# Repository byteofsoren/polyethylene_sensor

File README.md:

# polyethylene_sensor
Using High Density Conductive Polyethylene Black Foam as a restive sensor to build spatial object awareness in robotic grippers

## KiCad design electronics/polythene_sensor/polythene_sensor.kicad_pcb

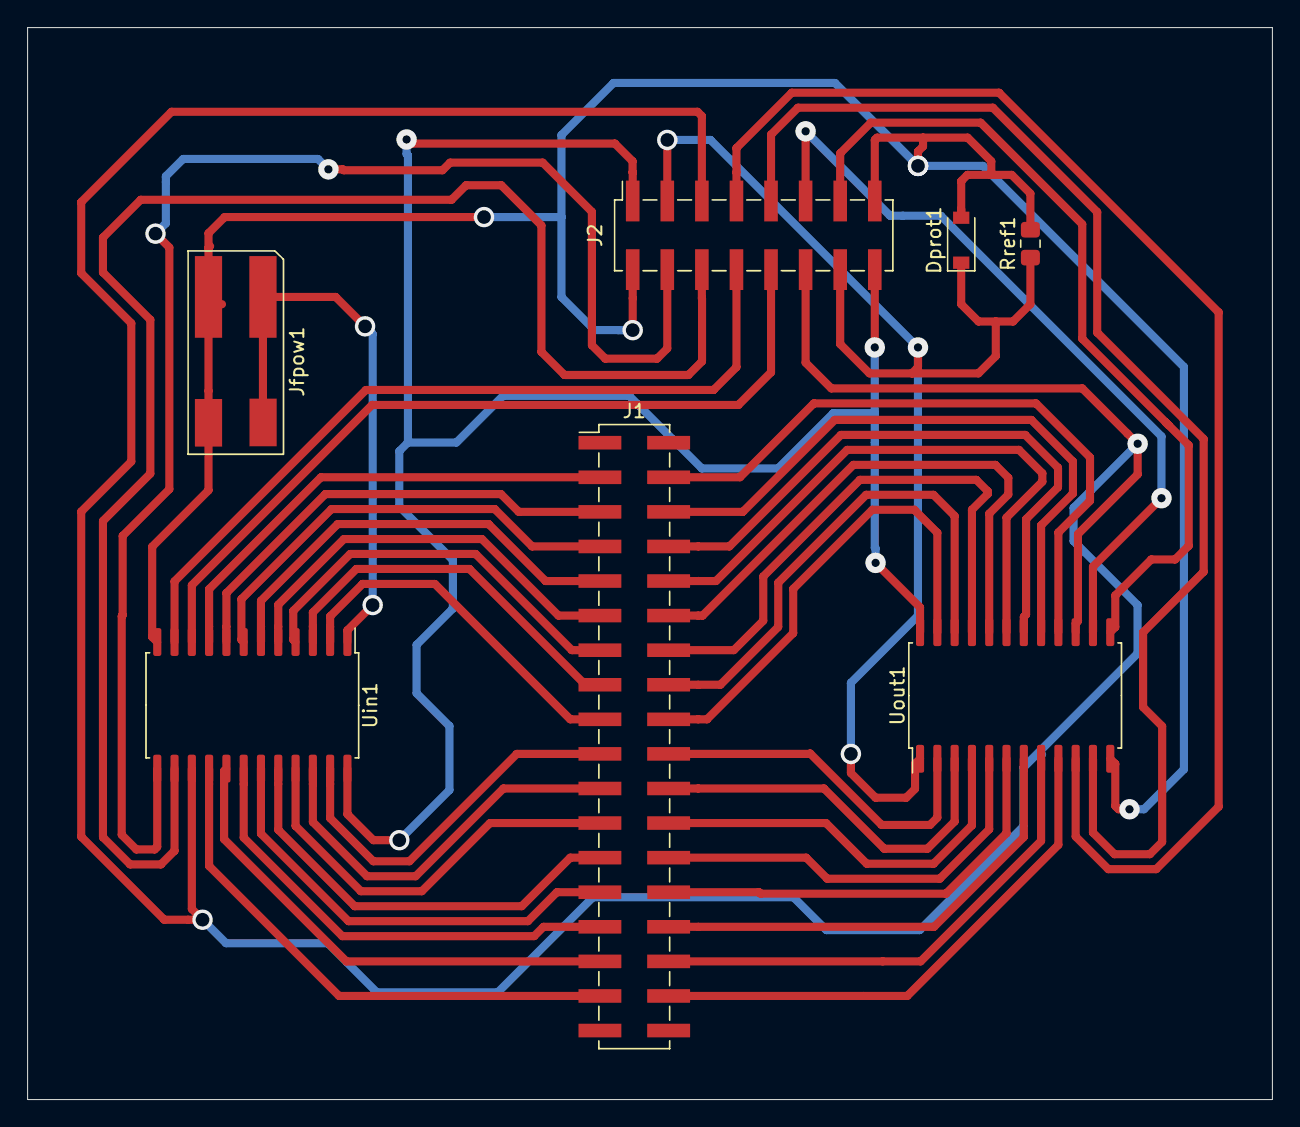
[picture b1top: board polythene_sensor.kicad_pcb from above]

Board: 2 copper layers, 91.4 x 78.7 mm, 7 parts (0 on the bottom side), 45 nets.

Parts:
Dprot1: BZT52Bxx; D_SOD-123
J1: Conn_02x18_Odd_Even; PinHeader_2x18_P2.54mm_Vertical_SMD
J2: Conn_02x08_Odd_Even; PinSocket_2x08_P2.54mm_Vertical_SMD
Jfpow1: Conn_01x02; MOLEX_104188
Rref1: R; R_0805_2012Metric_Pad1.15x1.40mm_HandSolder
Uin1: CD74HC4067M; SOIC-24W_7.5x15.4mm_P1.27mm
Uout1: CD74HC4067M; SOIC-24W_7.5x15.4mm_P1.27mm

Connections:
+5V: J2.1, J2.16, Uin1.24, Uout1.24
/EN: J2.5, J2.12, Uin1.15, Uout1.15
/S0: J2.13, Uout1.13
/S1: J2.11, Uout1.14
/S2: J2.9, Uout1.11
/S3: J2.7, Uout1.10
/S4: J2.10, Uin1.10
/S5: J2.8, Uin1.11
/S6: J2.6, Uin1.14
/S7: J2.4, Uin1.13
GND: Dprot1.2, J2.2, J2.15, Jfpow1.2, Rref1.2, Uin1.12, Uout1.12
unnamed: Dprot1.1, J2.3, J2.14, Rref1.1, Uout1.1
unnamed: J1.3, Uin1.9
unnamed: J1.4, Uout1.16
unnamed: J1.5, Uin1.8
unnamed: J1.6, Uout1.17
unnamed: J1.7, Uin1.7
unnamed: J1.8, Uout1.18
unnamed: J1.9, Uin1.6
unnamed: J1.10, Uout1.19
unnamed: J1.11, Uin1.5
unnamed: J1.12, Uout1.20
unnamed: J1.13, Uin1.4
unnamed: J1.14, Uout1.21
unnamed: J1.15, Uin1.3
unnamed: J1.16, Uout1.22
unnamed: J1.17, Uin1.2
unnamed: J1.18, Uout1.23
unnamed: J1.19, Uin1.23
unnamed: J1.20, Uout1.2
unnamed: J1.21, Uin1.22
unnamed: J1.22, Uout1.3
unnamed: J1.23, Uin1.21
unnamed: J1.24, Uout1.4
unnamed: J1.25, Uin1.20
unnamed: J1.26, Uout1.5
unnamed: J1.27, Uin1.19
unnamed: J1.28, Uout1.6
unnamed: J1.29, Uin1.18
unnamed: J1.30, Uout1.7
unnamed: J1.31, Uin1.17
unnamed: J1.32, Uout1.8
unnamed: J1.33, Uin1.16
unnamed: J1.34, Uout1.9
unnamed: Jfpow1.1, Uin1.1

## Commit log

2019-05-01 start project
2019-05-01 added ycm_extra_conf.py and main.cpp
2019-05-01 woring on setting the mux
2019-05-06 Bord ready
2019-05-08 Board ready
2019-05-08 added board files
2019-05-16 Added .CSV lists
2019-05-16 Updated parts
2019-05-17 changed the electronics to sute the new board
2019-05-17 Updated in the electronics
2019-05-20 Ddata from client to server works
2019-05-24 Conversion perhaps works
2019-05-27 Python code is working (i think)
2019-05-28 woring on the presentation
2019-05-30 added missing point
2019-05-30 fixed
2019-05-30 fixed 2
2019-05-30 Added testing file
2019-05-30 woriding on show3d
2019-05-30 pushed
2019-05-30 Added [ ] in test file
2019-05-30 Added matrix and Array in test gen, resaved testArray
2019-05-30 renamed
2019-05-30 added testArray data suport to main_arduino.py
2019-05-30 Pic for pres and some formation
2019-05-30 created test
2019-05-30 added image
2019-05-30 crop pic
2019-05-30 text complete
2019-05-30 first 2
2019-05-30 edditing
2019-06-05 Presentation finiched
2019-06-06 stat and pics
2019-06-07 data from wheight
2019-06-07 Auto stash before merge of "master" and "origin/master"
